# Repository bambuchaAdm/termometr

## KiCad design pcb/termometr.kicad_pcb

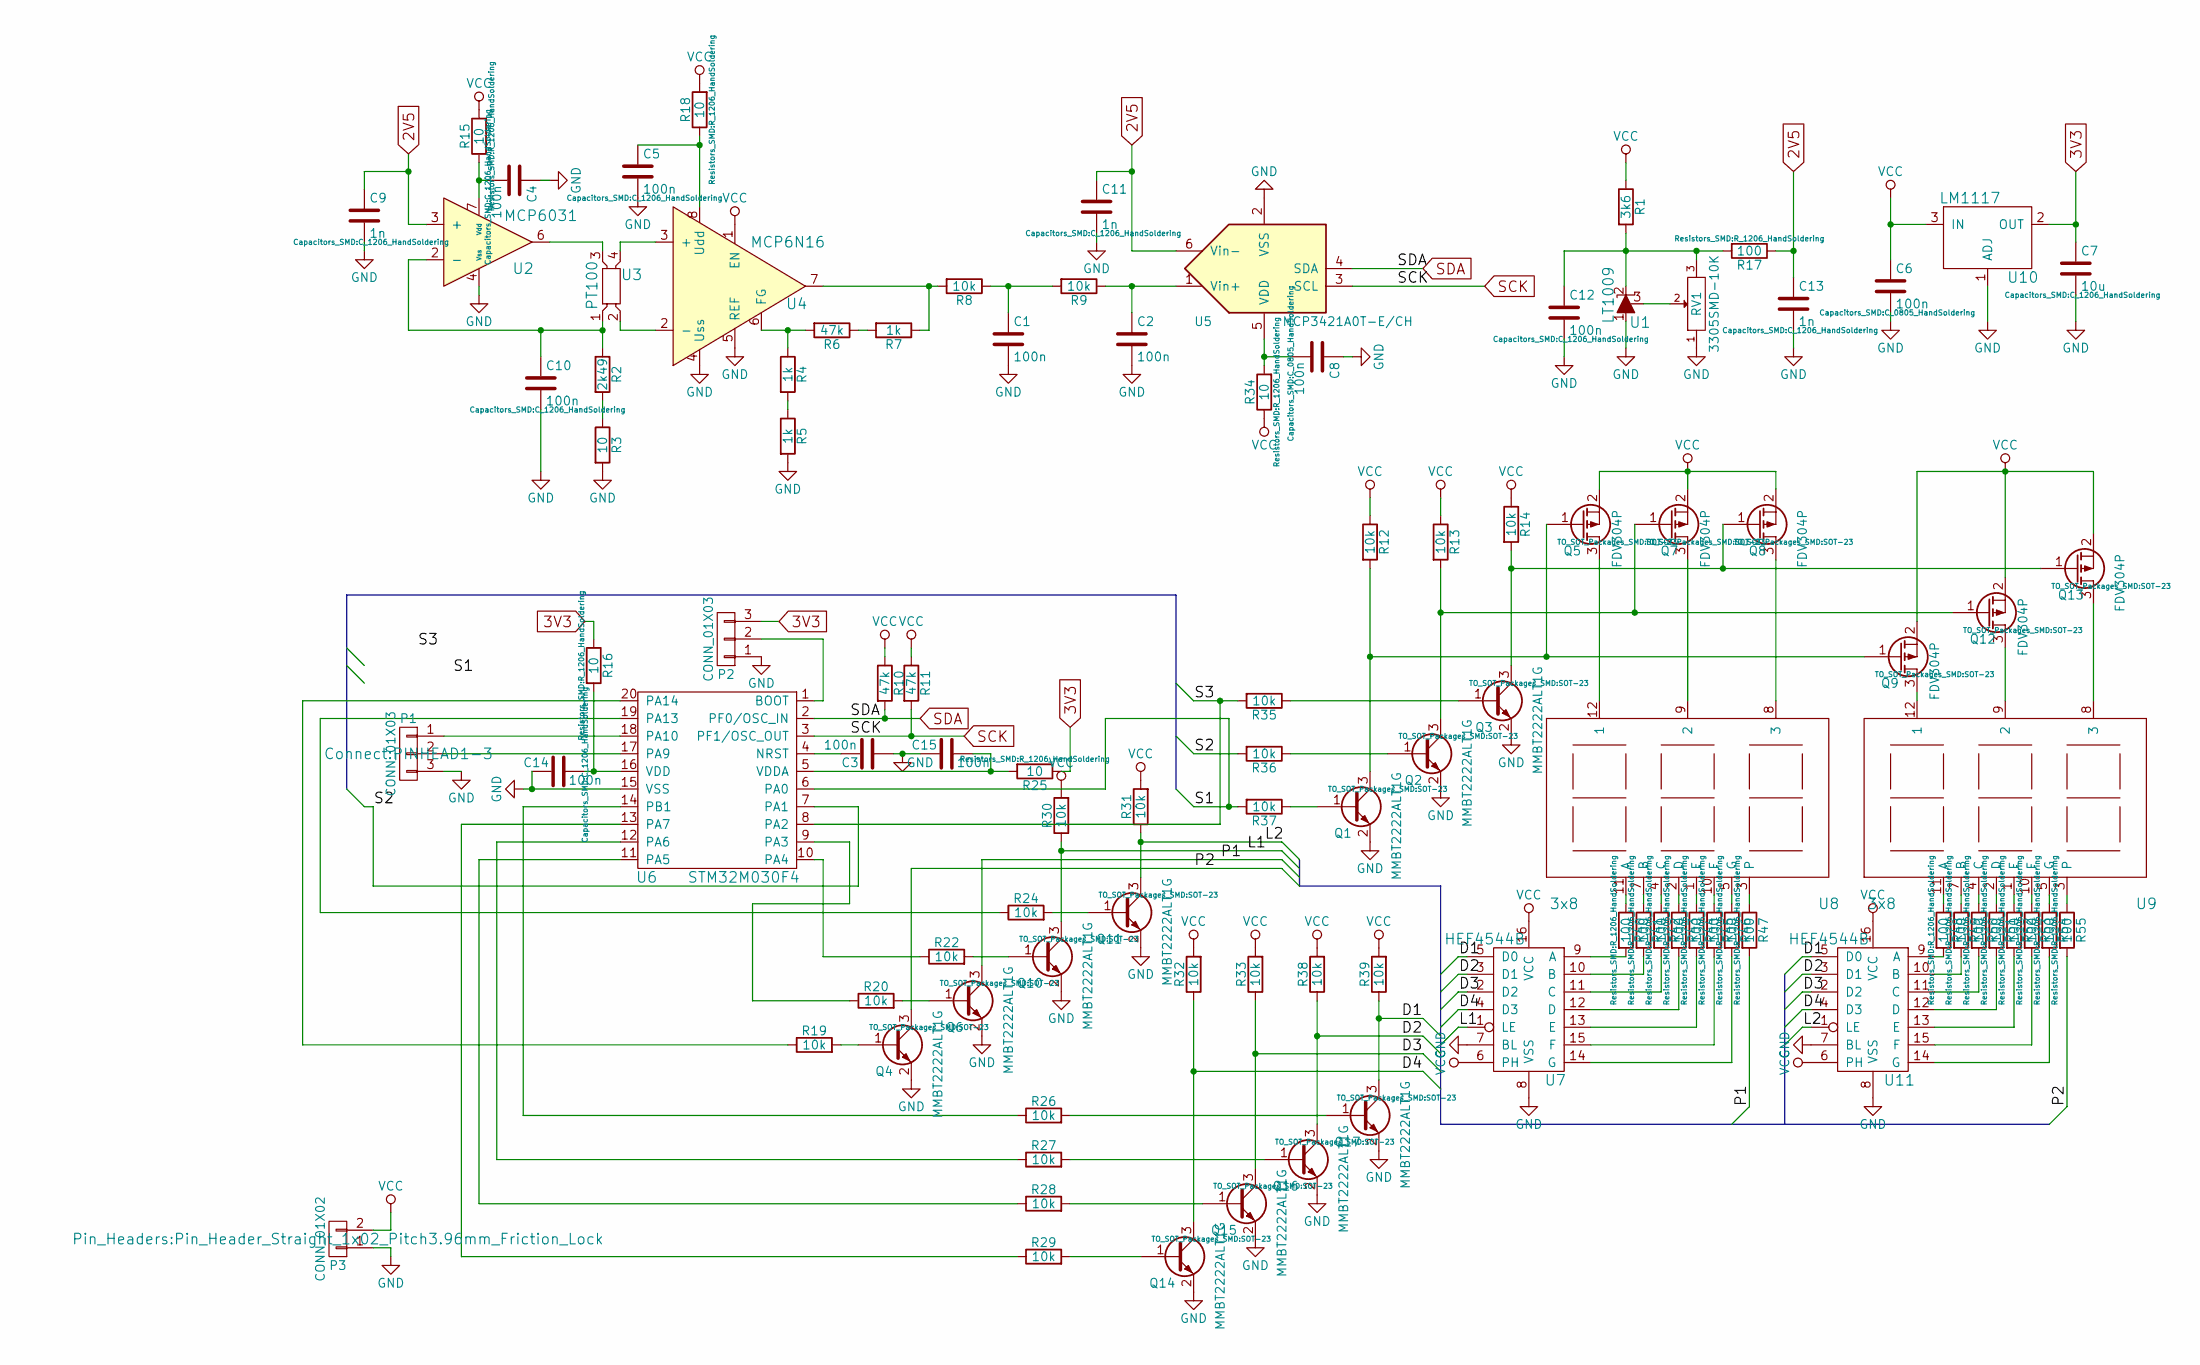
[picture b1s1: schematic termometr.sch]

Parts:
C1, C2, C6, C8: 100n; C_0805_HandSoldering
C3, C4, C5, C10, C12, C14, C15: 100n; C_1206_HandSoldering
C7: 10u; C_1206_HandSoldering
C9, C11, C13: 1n; C_1206_HandSoldering
P1, P2: CONN_01X03; PINHEAD1-3
P3: CONN_01X02; Pin_Header_Straight_1x02_Pitch3.96mm_Friction_Lock
Q1, Q2, Q3, Q4, Q6, Q10, Q11, Q14, Q15, Q16, Q17: MMBT2222ALT1G; SOT-23
Q5, Q7, Q8, Q9, Q12, Q13: FDV304P; SOT-23
R1: 3k6; R_1206_HandSoldering
R2: 2k49; R_0805_HandSoldering; Tolerance 0.1%
R3: 10; R_0805_HandSoldering; Tolerance 0.1%
R4, R5, R7: 1k; R_0805_HandSoldering; Tolerance 0.1%
R6: 47k; R_0805_HandSoldering; Tolerance 0.1
R8, R9: 10k; R_0805_HandSoldering
R10, R11: 47k; R_0805_HandSoldering
R12, R13, R14, R19, R20, R22, R24, R26, R27, R28, R29, R30, R31, R32, R33, R35, R36, R37, R38, R39: 10k; R_1206_HandSoldering
R15, R16, R18, R25, R34: 10; R_1206_HandSoldering
R17, R40, R41, R42, R43, R44, R45, R46, R47, R48, R49, R50, R51, R52, R53, R54, R55: 100; R_1206_HandSoldering
RV1: 3305SMD-10K; 3305SMD
U1: LT1009; TO-92_Inline_Narrow_Oval
U2: MCP6031; MSOP-8_3x3mm_Pitch0.65mm
U3: PT100; Pin_Header_Straight_2x02
U4: MCP6N16; MSOP-8_3x3mm_Pitch0.65mm
U5: MCP3421A0T-E/CH; SOT-23-6
U6: STM32M030F4; TSSOP-20_4.4x6.5mm_Pitch0.65mm
U7, U11: HEF4544B; DIP-16_W7.62mm_LongPads
U8, U9: 3x8; 3x7segment
U10: LM1117; SOT-223

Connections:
2V5: C9.1, C11.1, C13.1, R17.1, U2.3 (+), U5.6 (Vin-)
3V3: C7.1, P2.3, R16.1, R25.1, U10.2 (OUT)
/D1: Q17.3 (C), R39.1, U7.5 (D0), U11.5 (D0)
/D2: Q16.3 (C), R38.1, U7.3 (D1), U11.3 (D1)
/D3: Q15.3 (C), R33.1, U7.2 (D2), U11.2 (D2)
/D4: Q14.3 (C), R32.1, U7.4 (D3), U11.4 (D3)
/L1: Q10.3 (C), R30.1, U7.1 (LE)
/L2: Q11.3 (C), R31.1, U11.1 (LE)
/P1: Q6.3 (C), R47.2
/P2: Q4.3 (C), R55.2
/S2: R36.2, U6.7 (PA1)
/S3: R35.2, U6.8 (PA2)
GND: C1.2, C2.2, C3.1, C4.1, C5.2, C6.2, C7.2, C8.1, C9.2, C10.2, C11.2, C12.2, C13.2, C14.1, C15.1, P1.3, P2.1, P3.1, Q1.2 (E), Q2.2 (E), Q3.2 (E), Q4.2 (E), Q6.2 (E), Q10.2 (E), Q11.2 (E), Q14.2 (E), Q15.2 (E), Q16.2 (E), Q17.2 (E), R3.2, R5.2, RV1.1, U1.1, U2.4 (Vss), U4.4 (Uss), U4.5 (REF), U5.2 (VSS), U6.15 (VSS), U7.7 (BL), U7.8 (VSS), U10.1 (ADJ), U11.7 (BL), U11.8 (VSS)
unnamed: C1.1, R8.1, R9.2
unnamed: C2.1, R9.1, U5.1 (Vin+)
unnamed: C3.2, U6.4 (NRST)
unnamed: C4.2, R15.1, U2.7 (Vdd)
unnamed: C5.1, R18.1, U4.8 (Udd)
unnamed: C8.2, R34.2, U5.5 (VDD)
unnamed: C10.1, R2.1, U2.2 (-), U3.1
unnamed: C12.1, R1.2, R17.2, RV1.3, U1.2
unnamed: C14.2, R16.2, U6.16 (VDD)
unnamed: C15.2, R25.2, U6.5 (VDDA)
unnamed: P1.1, U6.18 (PA10)
unnamed: P1.2, U6.17 (PA9)
unnamed: P2.2, U6.1 (BOOT)
unnamed: Q1.1 (B), R37.1
unnamed: Q1.3 (C), Q5.1 (G), Q9.1 (G), R12.2
unnamed: Q2.1 (B), R36.1
unnamed: Q3.1 (B), R35.1
unnamed: Q4.1 (B), R19.2
unnamed: Q5.3 (D), U8.12 (1)
unnamed: Q6.1 (B), R20.2
unnamed: Q7.3 (D), U8.9 (2)
unnamed: Q8.3 (D), U8.8 (3)
unnamed: Q9.3 (D), U9.12 (1)
unnamed: Q10.1 (B), R22.2
unnamed: Q11.1 (B), R24.2
unnamed: Q2.3 (C), Q7.1 (G), Q12.1 (G), R13.2
unnamed: Q12.3 (D), U9.9 (2)
unnamed: Q3.3 (C), Q8.1 (G), Q13.1 (G), R14.2
unnamed: Q13.3 (D), U9.8 (3)
unnamed: Q14.1 (B), R29.2
unnamed: Q15.1 (B), R28.2
unnamed: Q16.1 (B), R27.2
unnamed: Q17.1 (B), R26.2
unnamed: R2.2, R3.1
unnamed: R4.1, R6.2, U4.6 (FG)
unnamed: R4.2, R5.1
unnamed: R6.1, R7.2
unnamed: R7.1, R8.2, U4.7
unnamed: R19.1, U6.20 (PA14)
unnamed: R20.1, U6.9 (PA3)
unnamed: R22.1, U6.10 (PA4)
unnamed: R24.1, U6.19 (PA13)
unnamed: R26.1, U6.14 (PB1)
unnamed: R27.1, U6.12 (PA6)
unnamed: R28.1, U6.11 (PA5)
unnamed: R29.1, U6.13 (PA7)
unnamed: R40.1, U8.11 (A)
unnamed: R40.2, U7.9 (A)
unnamed: R41.1, U8.7 (B)
unnamed: R41.2, U7.10 (B)
unnamed: R42.1, U8.4 (C)
unnamed: R42.2, U7.11 (C)
unnamed: R43.1, U8.2 (D)
unnamed: R43.2, U7.12 (D)
unnamed: R44.1, U8.1 (E)
unnamed: R44.2, U7.13 (E)
unnamed: R45.1, U8.10 (F)
unnamed: R45.2, U7.15 (F)
unnamed: R46.1, U8.5 (G)
unnamed: R46.2, U7.14 (G)
unnamed: R47.1, U8.3
unnamed: R48.1, U9.11 (A)
unnamed: R48.2, U11.9 (A)
unnamed: R49.1, U9.7 (B)
unnamed: R49.2, U11.10 (B)
unnamed: R50.1, U9.4 (C)
unnamed: R50.2, U11.11 (C)
unnamed: R51.1, U9.2 (D)
unnamed: R51.2, U11.12 (D)
unnamed: R52.1, U9.1 (E)
unnamed: R52.2, U11.13 (E)
unnamed: R53.1, U9.10 (F)
unnamed: R53.2, U11.15 (F)
unnamed: R54.1, U9.5 (G)
unnamed: R54.2, U11.14 (G)
unnamed: R55.1, U9.3
unnamed: RV1.2, U1.3
unnamed: U2.6, U3.3
unnamed: U3.2, U4.2 (-)
unnamed: U3.4, U4.3 (+)
SCK: R11.2, U5.3 (SCL), U6.3 (PF1/OSC_OUT)
SDA: R10.2, U5.4 (SDA), U6.2 (PF0/OSC_IN)

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
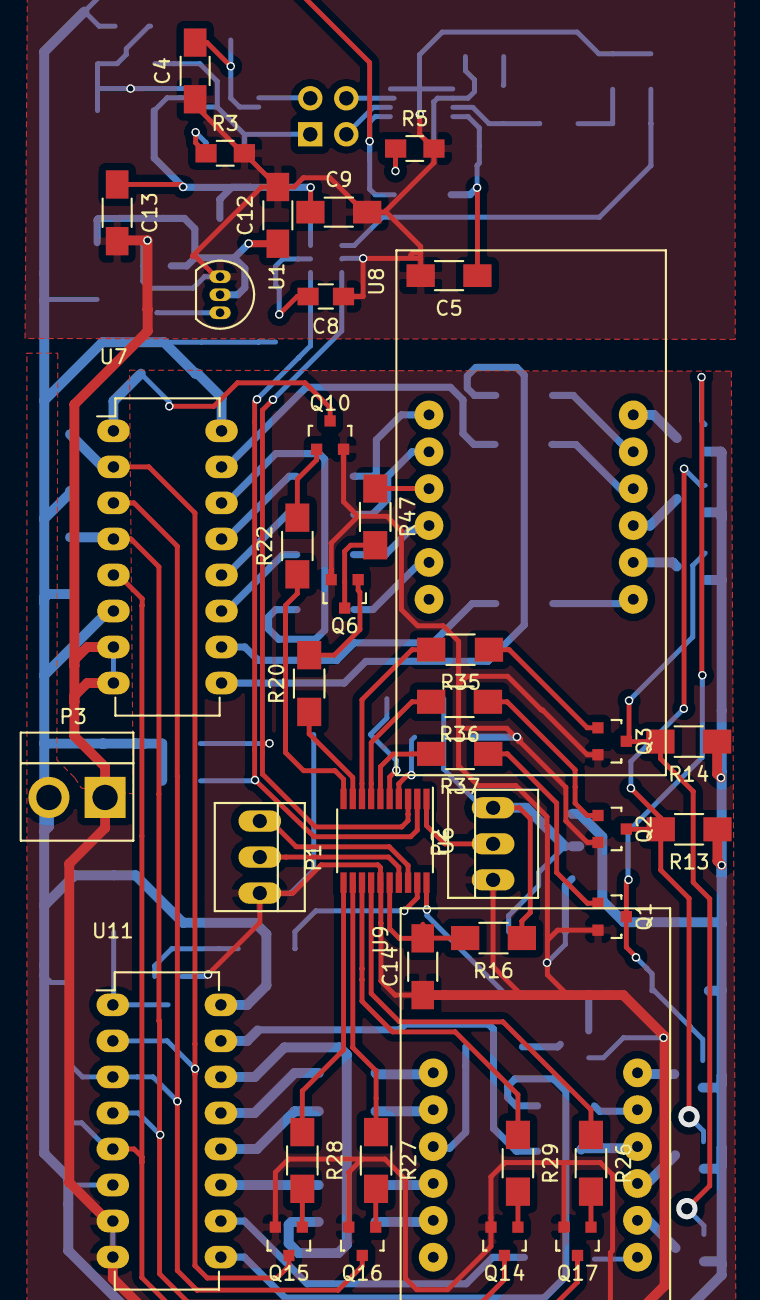
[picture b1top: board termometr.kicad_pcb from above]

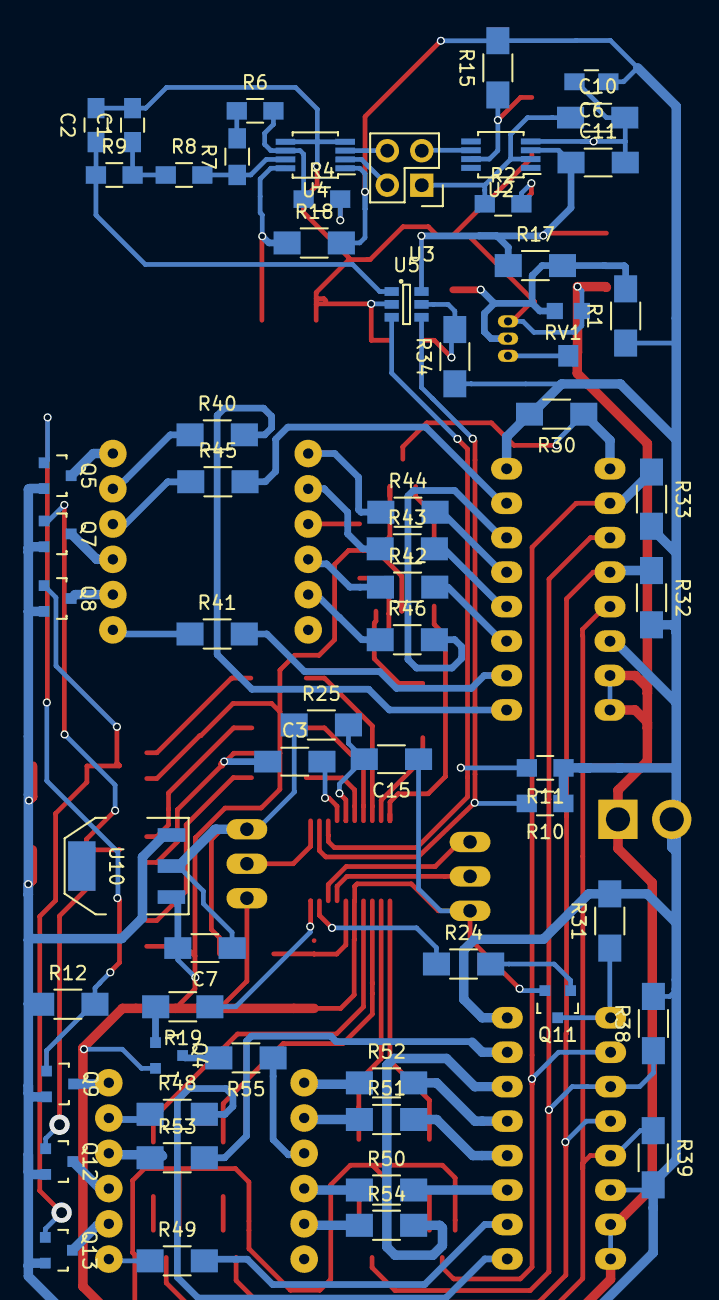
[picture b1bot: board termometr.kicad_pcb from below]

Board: 2 copper layers, 100 parts (60 on the bottom side), 97 nets.

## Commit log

2015-12-06 Initial commit
    Reference documentation for parts.
2015-12-06 First version of PCB
2015-12-26 Next version. First iteration.
2015-12-28 All connected with zones.
